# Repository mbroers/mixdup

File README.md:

# mixdup
teensy based midi controller

Based on the awesome [Control Surface](https://github.com/tttapa/Control-Surface) teensyduino library.

v1 has two rows of switches and uses teensy 3.2

v2 has 3 rows of switches, ICs moved to back of board so they are socketable (this resulted in a change to the teensy code as well), and the pots/sliders are a bit more spaced out along with some other minor cleanups. Still uses teensy 3.2

v3 is for teensy 4.1

Forthcoming
- [ ] Panel vector/FPE files
- [ ] Enclosure plans
- [ ] Expander with Effects Racks capabilities and 5 band eq
- [ ] Live macros to create default map

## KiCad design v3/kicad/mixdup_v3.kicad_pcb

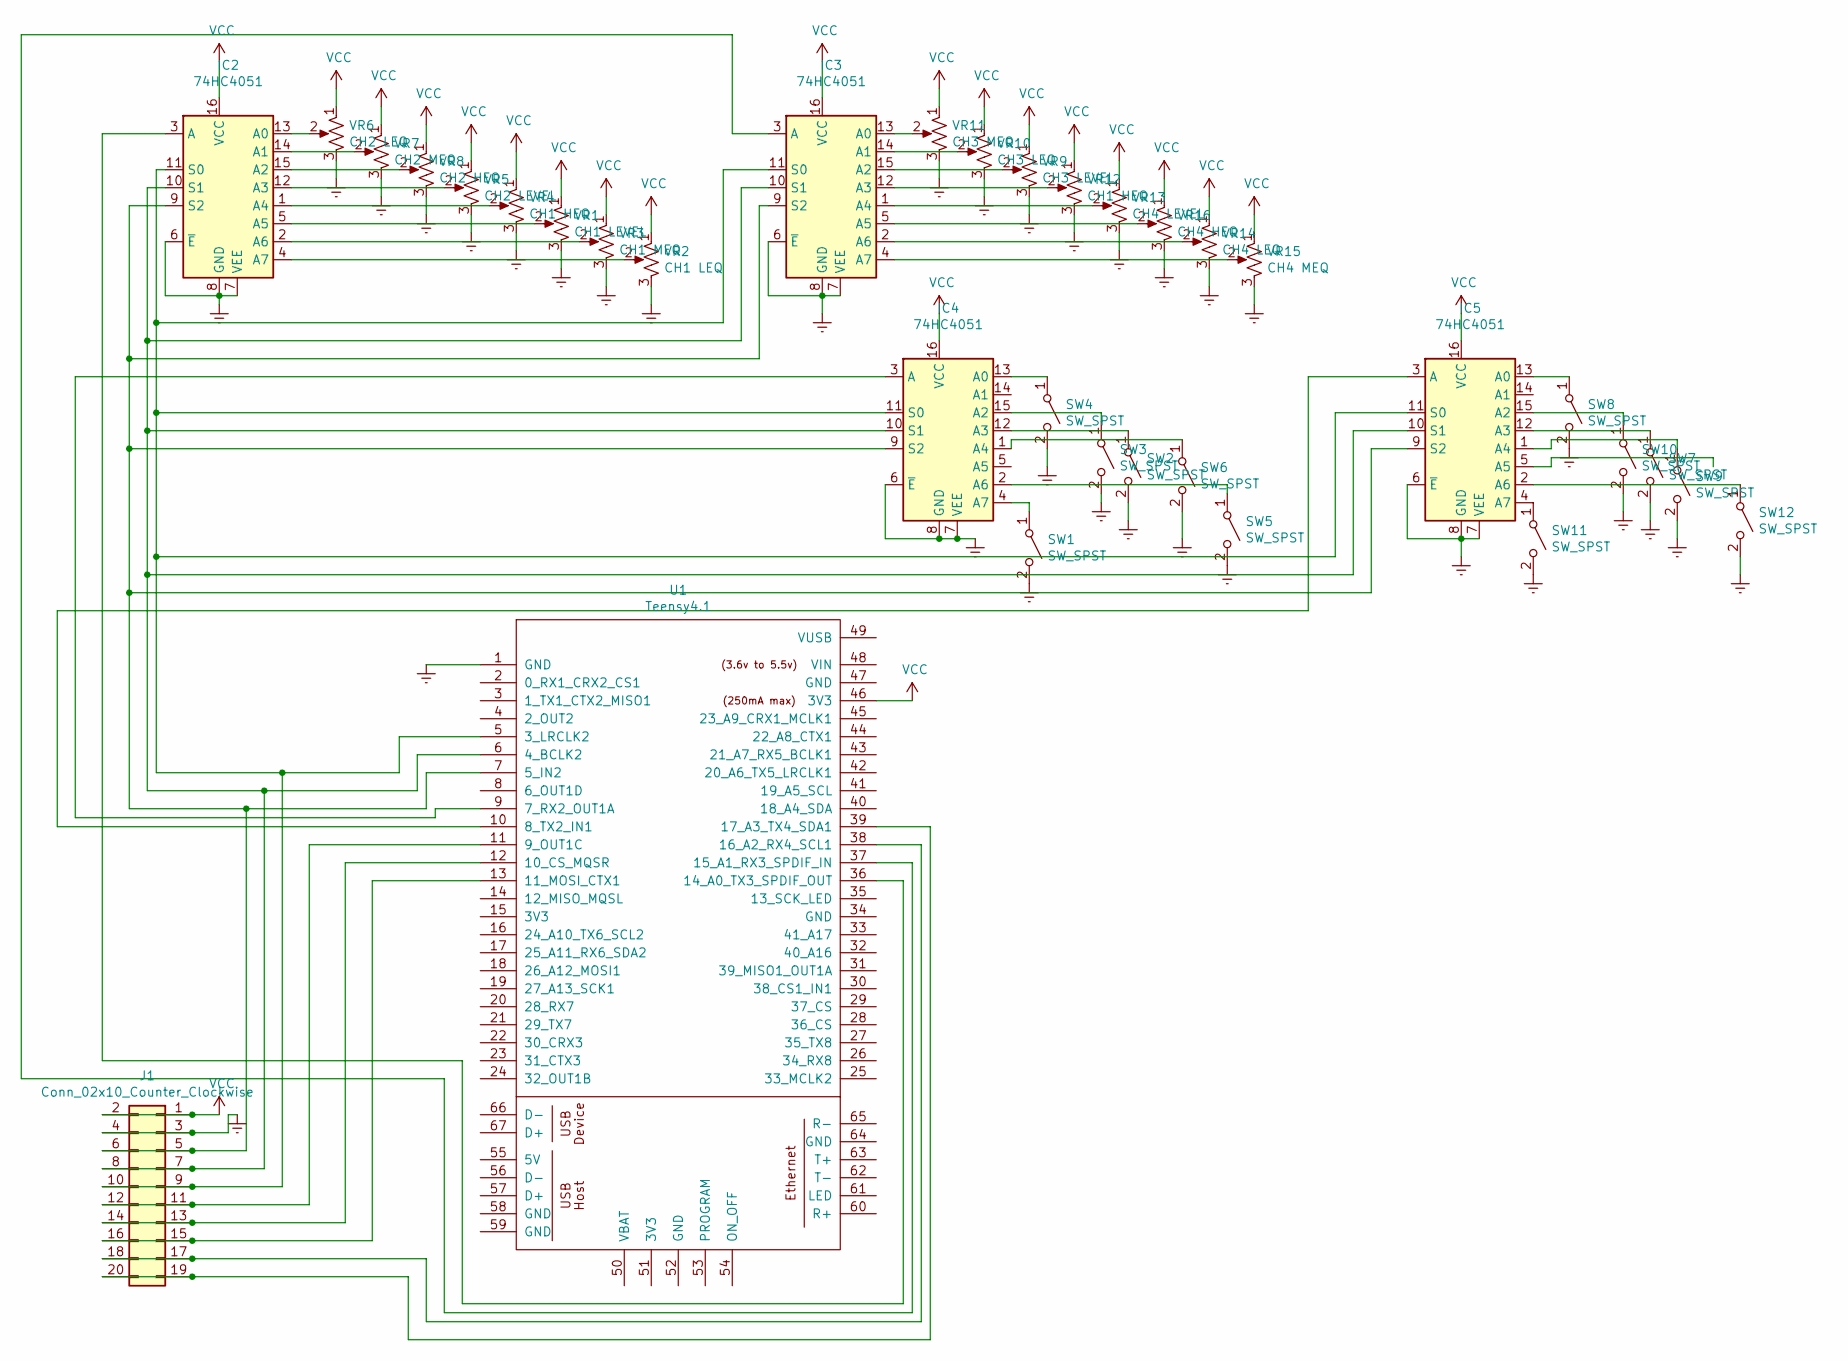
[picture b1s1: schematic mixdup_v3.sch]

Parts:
IC2, IC3, IC4, IC5: 74HC4051; DIP794W45P254L1969H508Q16
J1: Conn_02x10_Counter_Clockwise; PinHeader_2x10_P2.54mm_Vertical
SW1, SW2, SW3, SW4, SW5, SW6, SW7, SW8, SW9, SW10, SW11, SW12: SW_SPST; SW_D6R90_F1_LFS
U1: Teensy4.1; Teensy41
VR1: CH1 LEVEL; PTA4543-2015DPA103
VR2: CH1 LEQ; RD901F-ALPHA-POT
VR3: CH1 MEQ; RD901F-ALPHA-POT
VR4, VR12: CH1 HEQ; RD901F-ALPHA-POT
VR5: CH2 LEVEL; PTA4543-2015DPA103
VR6: CH2 LEQ; RD901F-ALPHA-POT
VR7: CH2 MEQ; RD901F-ALPHA-POT
VR8: CH2 HEQ; RD901F-ALPHA-POT
VR9: CH3 LEVEL; PTA4543-2015DPA103
VR10: CH3 LEQ; RD901F-ALPHA-POT
VR11: CH3 MEQ; RD901F-ALPHA-POT
VR13: CH4 LEVEL; PTA4543-2015DPA103
VR14: CH4 LEQ; RD901F-ALPHA-POT
VR15: CH4 MEQ; RD901F-ALPHA-POT
VR16: CH4 HEQ; RD901F-ALPHA-POT

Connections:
Earth: IC2.6 (~E), IC2.7 (VEE), IC2.8 (GND), IC3.6 (~E), IC3.7 (VEE), IC3.8 (GND), IC4.6 (~E), IC4.7 (VEE), IC4.8 (GND), IC5.6 (~E), IC5.7 (VEE), IC5.8 (GND), J1.3, J1.4, SW1.2 (B), SW2.2 (B), SW3.2 (B), SW4.2 (B), SW5.2 (B), SW6.2 (B), SW7.2 (B), SW8.2 (B), SW9.2 (B), SW10.2 (B), SW11.2 (B), SW12.2 (B), U1.1 (GND), VR1.3, VR2.3, VR3.3, VR4.3, VR5.3, VR6.3, VR7.3, VR8.3, VR9.3, VR10.3, VR11.3, VR12.3, VR13.3, VR14.3, VR15.3, VR16.3
unnamed: IC2.1 (A4), VR4.2
unnamed: IC2.2 (A6), VR3.2
unnamed: IC2.3 (A), U1.36 (14_A0_TX3_SPDIF_OUT)
unnamed: IC2.4 (A7), VR2.2
unnamed: IC2.5 (A5), VR1.2
unnamed: IC2.9 (S2), IC3.9 (S2), IC4.9 (S2), IC5.9 (S2), J1.5, J1.6, U1.7 (5_IN2)
unnamed: IC2.10 (S1), IC3.10 (S1), IC4.10 (S1), IC5.10 (S1), J1.7, J1.8, U1.6 (4_BCLK2)
unnamed: IC2.11 (S0), IC3.11 (S0), IC4.11 (S0), IC5.11 (S0), J1.9, J1.10, U1.5 (3_LRCLK2)
unnamed: IC2.12 (A3), VR5.2
unnamed: IC2.13 (A0), VR6.2
unnamed: IC2.14 (A1), VR7.2
unnamed: IC2.15 (A2), VR8.2
unnamed: IC3.1 (A4), VR13.2
unnamed: IC3.2 (A6), VR14.2
unnamed: IC3.3 (A), U1.37 (15_A1_RX3_SPDIF_IN)
unnamed: IC3.4 (A7), VR15.2
unnamed: IC3.5 (A5), VR16.2
unnamed: IC3.12 (A3), VR12.2
unnamed: IC3.13 (A0), VR11.2
unnamed: IC3.14 (A1), VR10.2
unnamed: IC3.15 (A2), VR9.2
unnamed: IC4.1 (A4), SW6.1 (A)
unnamed: IC4.2 (A6), SW5.1 (A)
unnamed: IC4.3 (A), U1.9 (7_RX2_OUT1A)
unnamed: IC4.4 (A7), SW1.1 (A)
unnamed: IC4.12 (A3), SW2.1 (A)
unnamed: IC4.13 (A0), SW4.1 (A)
unnamed: IC4.15 (A2), SW3.1 (A)
unnamed: IC5.1 (A4), SW9.1 (A)
unnamed: IC5.2 (A6), SW12.1 (A)
unnamed: IC5.3 (A), U1.10 (8_TX2_IN1)
unnamed: IC5.4 (A7), SW11.1 (A)
unnamed: IC5.12 (A3), SW7.1 (A)
unnamed: IC5.13 (A0), SW8.1 (A)
unnamed: IC5.15 (A2), SW10.1 (A)
unnamed: J1.11, J1.12, U1.11 (9_OUT1C)
unnamed: J1.13, J1.14, U1.12 (10_CS_MQSR)
unnamed: J1.15, J1.16, U1.13 (11_MOSI_CTX1)
unnamed: J1.17, J1.18, U1.38 (16_A2_RX4_SCL1)
unnamed: J1.19, J1.20, U1.39 (17_A3_TX4_SDA1)
VCC: IC2.16 (VCC), IC3.16 (VCC), IC4.16 (VCC), IC5.16 (VCC), J1.1, J1.2, U1.46 (3V3), VR1.1, VR2.1, VR3.1, VR4.1, VR5.1, VR6.1, VR7.1, VR8.1, VR9.1, VR10.1, VR11.1, VR12.1, VR13.1, VR14.1, VR15.1, VR16.1

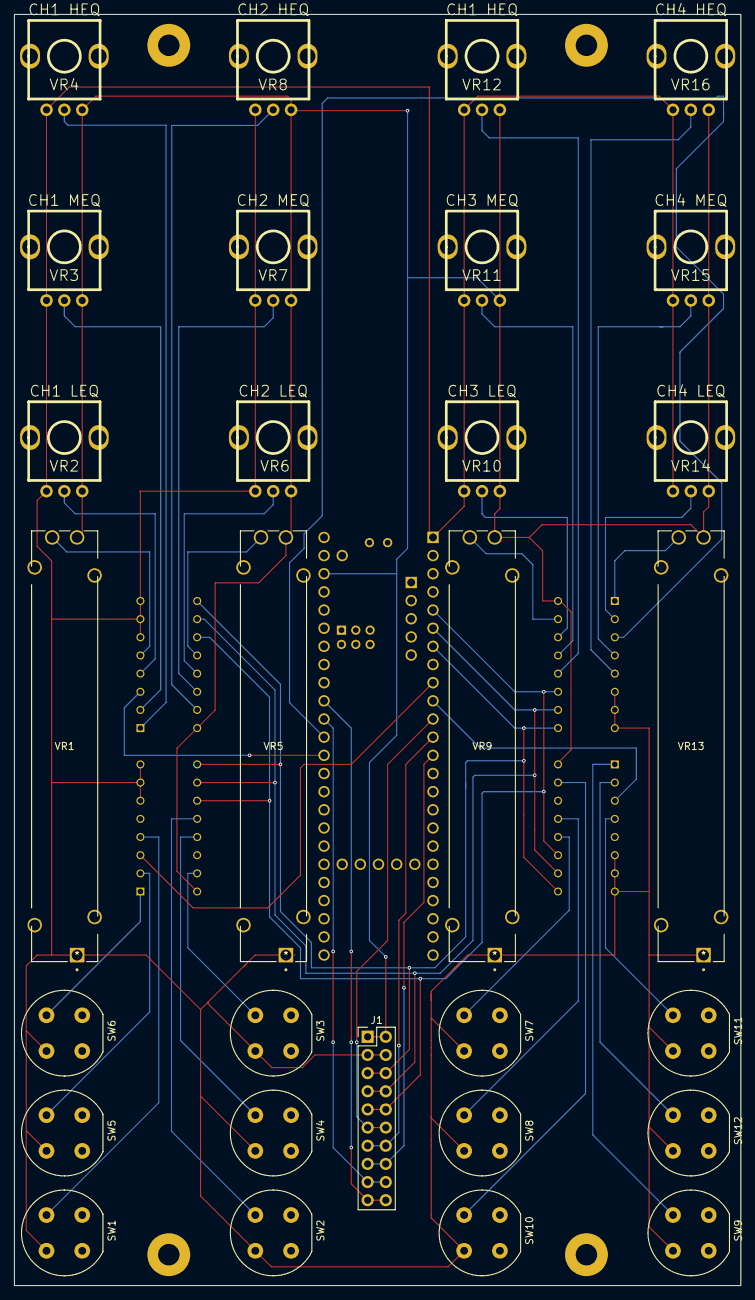
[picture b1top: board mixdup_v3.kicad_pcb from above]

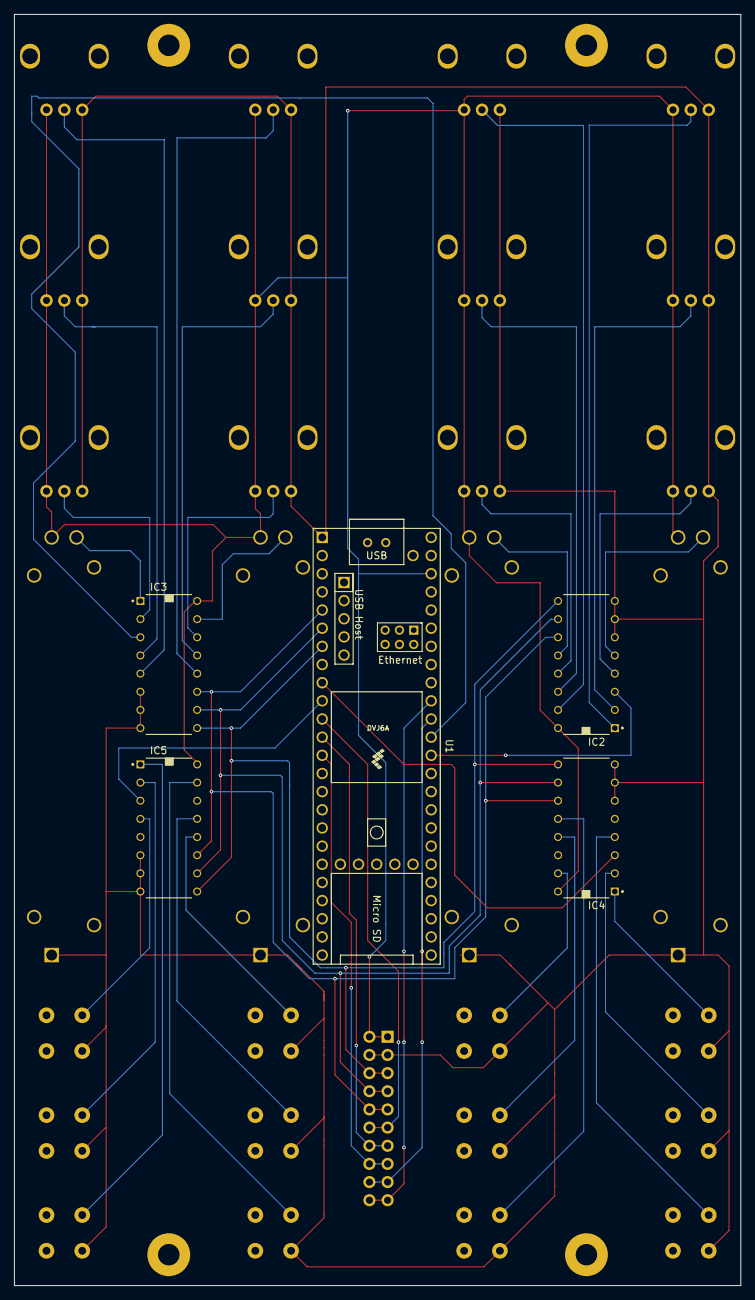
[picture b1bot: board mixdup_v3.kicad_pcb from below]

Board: 2 copper layers, 101.6 x 177.8 mm, 34 parts (5 on the bottom side), 42 nets.

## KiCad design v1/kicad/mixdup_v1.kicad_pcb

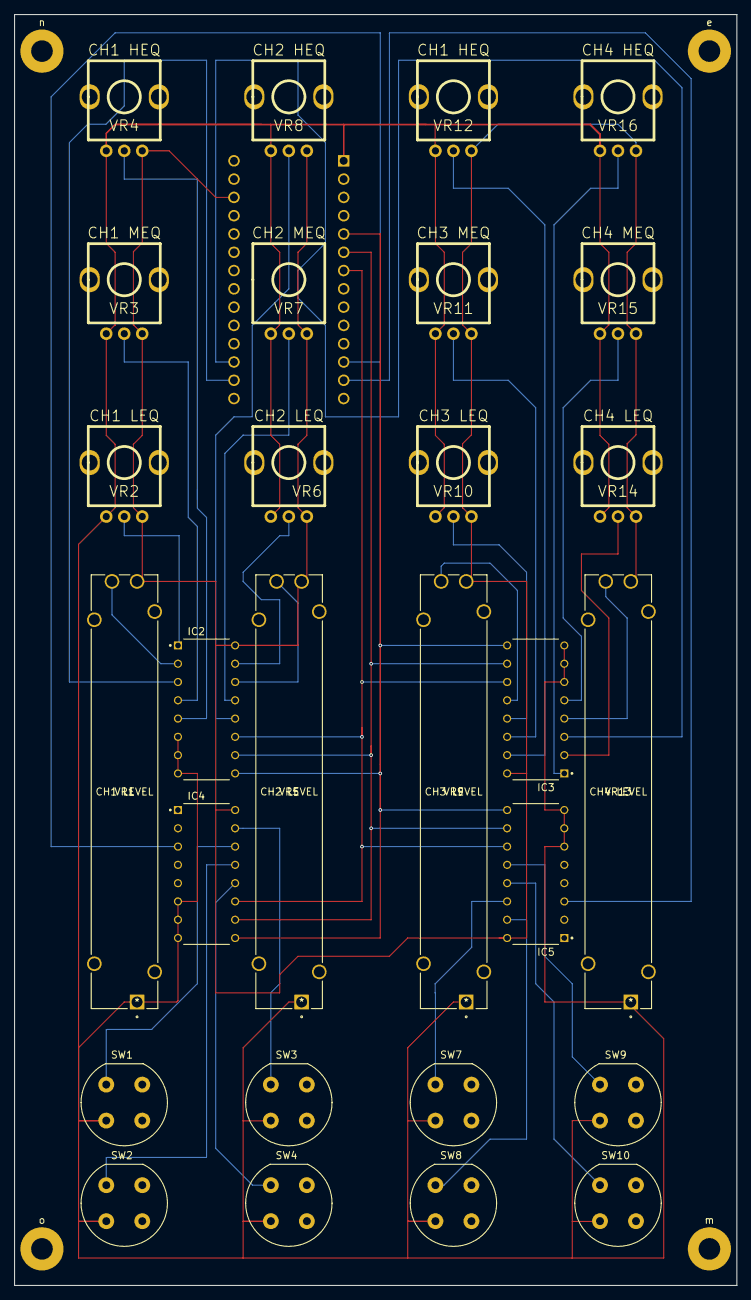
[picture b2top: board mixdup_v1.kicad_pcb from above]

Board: 2 copper layers, 100.3 x 176.5 mm, 33 parts (1 on the bottom side), 33 nets.

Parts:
IC1: Teensy3.2; Teensy30_31_32_Some_Pins_MB
IC2, IC3, IC4, IC5: 74HC4051; DIP794W45P254L1969H508Q16
SW1, SW2, SW3, SW4, SW7, SW8, SW9, SW10: SW_SPST; SW_D6R90_F1_LFS
VR1: CH1 LEVEL; PTA4543-2015DPA103
VR2: CH1 LEQ; RD901F-ALPHA-POT
VR3: CH1 MEQ; RD901F-ALPHA-POT
VR4, VR12: CH1 HEQ; RD901F-ALPHA-POT
VR5: CH2 LEVEL; PTA4543-2015DPA103
VR6: CH2 LEQ; RD901F-ALPHA-POT
VR7: CH2 MEQ; RD901F-ALPHA-POT_MB_overteensy
VR8: CH2 HEQ; RD901F-ALPHA-POT
VR9: CH3 LEVEL; PTA4543-2015DPA103
VR10: CH3 LEQ; RD901F-ALPHA-POT
VR11: CH3 MEQ; RD901F-ALPHA-POT
VR13: CH4 LEVEL; PTA4543-2015DPA103
VR14: CH4 LEQ; RD901F-ALPHA-POT
VR15: CH4 MEQ; RD901F-ALPHA-POT
VR16: CH4 HEQ; RD901F-ALPHA-POT
e: e; MountingHole_3mm_Pad
m: m; MountingHole_3mm_Pad
n: n; MountingHole_3mm_Pad
o: o; MountingHole_3mm_Pad

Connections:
Earth: IC1.1, IC2.6, IC2.7, IC2.8, IC3.6, IC3.7, IC3.8, IC4.6, IC4.7, IC4.8, IC5.6, IC5.7, IC5.8, SW1.2, SW2.2, SW3.2, SW4.2, SW7.2, SW8.2, SW9.2, SW10.2, VR1.3, VR2.3, VR3.3, VR4.3, VR5.3, VR6.3, VR7.3, VR8.3, VR9.3, VR10.3, VR11.3, VR12.3, VR13.3, VR14.3, VR15.3, VR16.3
unnamed: IC1.5, IC2.9, IC3.9, IC4.9, IC5.9
unnamed: IC1.6, IC2.10, IC3.10, IC4.10, IC5.10
unnamed: IC1.7, IC2.11, IC3.11, IC4.11, IC5.11
unnamed: IC1.12, IC4.3
unnamed: IC1.13, IC5.3
unnamed: IC1.21, IC2.3
unnamed: IC1.22, IC3.3
unnamed: IC2.1, VR2.2
unnamed: IC2.2, VR1.2
unnamed: IC2.4, VR3.2
unnamed: IC2.5, VR4.2
unnamed: IC2.12, VR8.2
unnamed: IC2.13, VR7.2
unnamed: IC2.14, VR5.2
unnamed: IC2.15, VR6.2
unnamed: IC3.1, VR16.2
unnamed: IC3.2, VR14.2
unnamed: IC3.4, VR13.2
unnamed: IC3.5, VR15.2
unnamed: IC3.12, VR9.2
unnamed: IC3.13, VR10.2
unnamed: IC3.14, VR11.2
unnamed: IC3.15, VR12.2
unnamed: IC4.12, SW4.1
unnamed: IC4.13, SW2.1
unnamed: IC4.14, SW1.1
unnamed: IC4.15, SW3.1
unnamed: IC5.12, SW9.1
unnamed: IC5.13, SW10.1
unnamed: IC5.14, SW7.1
unnamed: IC5.15, SW8.1
VCC: IC1.31, IC2.16, IC3.16, IC4.16, IC5.16, VR1.1, VR2.1, VR3.1, VR4.1, VR5.1, VR6.1, VR7.1, VR8.1, VR9.1, VR10.1, VR11.1, VR12.1, VR13.1, VR14.1, VR15.1, VR16.1

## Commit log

2021-12-20 adding an image
2021-12-20 removing ds store
2021-12-20 more removals
2021-12-20 final ds store removal
2021-12-20 adding image
2021-12-20 resizing
2022-01-30 components spaced out
2022-02-08 better spacing, ICs on back
2022-02-15 prototype ics on back better distro
2022-03-03 adding teensyduino file for v2
2022-03-06 fixed incorrect switch assignments
2022-03-14 adding bom for v2
2022-11-03 checkpoint - kicad great, panel needs tweaking
2022-11-03 updating for reference to teensy 4.1

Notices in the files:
parts and their libraries:
Copyright 2021 Accelerated Designs. All rights reserved.
